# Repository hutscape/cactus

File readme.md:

# Cactus

> 🌵 Indoor WiFi-connected temperature and humidity sensor 🍶

Visit [hutscape.com/cactus](https://hutscape.com/cactus/) for more details.

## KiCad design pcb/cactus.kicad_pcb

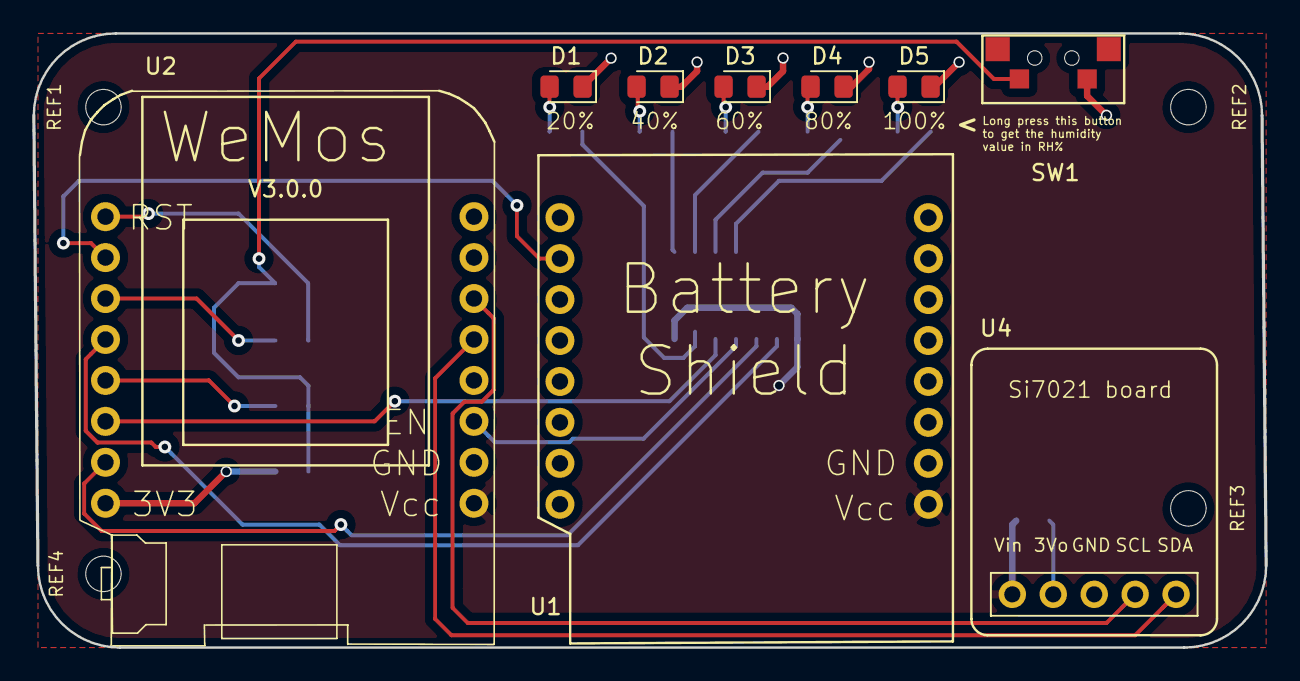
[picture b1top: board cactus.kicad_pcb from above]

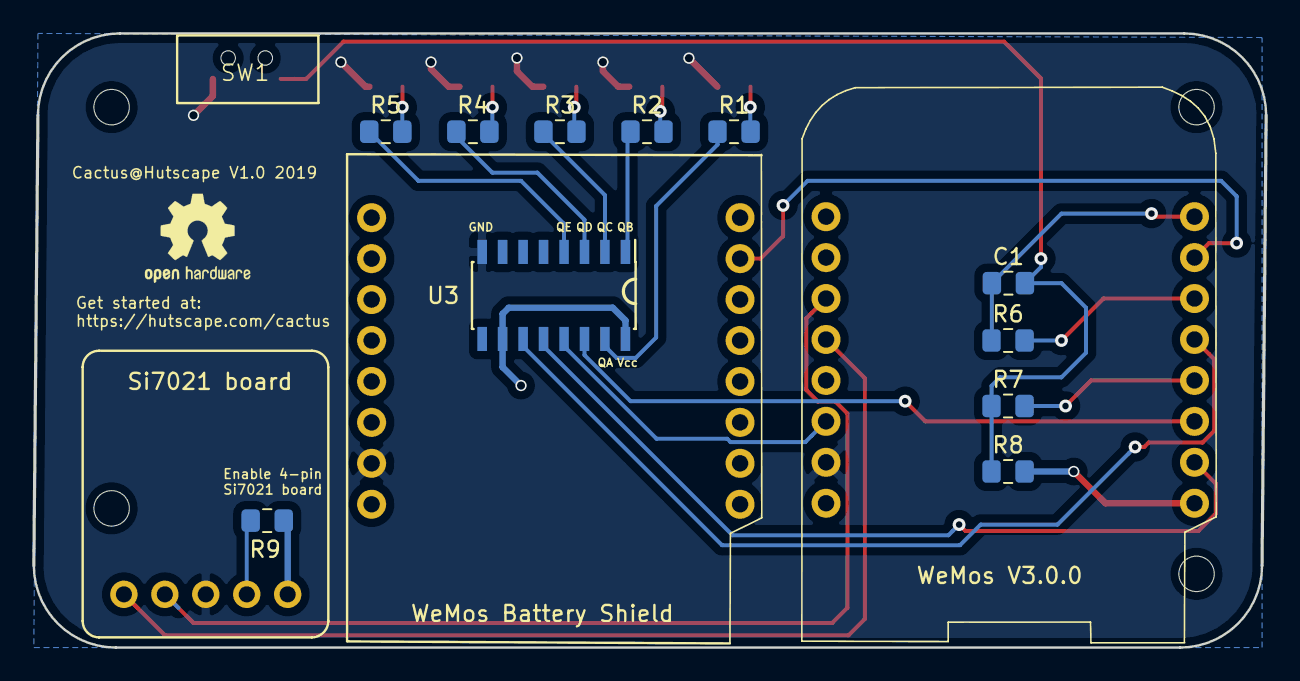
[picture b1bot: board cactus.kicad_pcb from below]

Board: 2 copper layers, 76.5 x 38.1 mm, 25 parts (12 on the bottom side), 25 nets.

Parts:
C1: 10u; C_0805_2012Metric_Pad1.15x1.40mm_HandSolder
D1, D2, D3, D4, D5: LED; LED_0805_2012Metric_Pad1.15x1.40mm_HandSolder
LOGO: OSHW-Logo2_7.3x6mm_SilkScreen
R1, R2, R3, R4, R5, R7: 1k; R_0805_2012Metric_Pad1.15x1.40mm_HandSolder
R6: 470; R_0805_2012Metric_Pad1.15x1.40mm_HandSolder
R8: 10k; R_0805_2012Metric_Pad1.15x1.40mm_HandSolder
R9: 0ohm; R_0805_2012Metric_Pad1.15x1.40mm_HandSolder
REF1, REF2, REF3, REF4: MountingHole_2.2mm_M2
SW1: SW_Push; Tactile_pushbutton
U1: WeMos_Battery_Shield; Battery_shield
U2: WeMos_D1_mini; D1_mini_board
U3: 74HC595; SOIC-16_3.9x9.9mm_P1.27mm
U4: Si7021_breakout; Si7021_breakout_board

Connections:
/3_3V: R8.2, U2.16
/A0: U1.10, U2.10
/D0: R6.2, U2.11
/D5: U2.12, U3.11
/D6: R7.2, U2.13
/D7: U2.14, U3.14
/D8: U2.15, U3.12
/EN: U2.3, U3.13
/I2C_SCL: U2.6, U4.2
/I2C_SDA: U2.5, U4.1
/QA: R1.1, U3.15
/QB: R2.1, U3.1
/QC: R3.1, U3.2
/QD: R4.1, U3.3
/QE: R5.1, U3.4
/RST: C1.1, R6.1, U2.9
GND: D1.1, D2.1, D3.1, D4.1, D5.1, SW1.2, U1.2, U2.2, U3.8, U4.3
unnamed: C1.2, R7.1, R8.1, SW1.1
unnamed: D1.2, R1.2
unnamed: D2.2, R2.2
unnamed: D3.2, R3.2
unnamed: D4.2, R4.2
unnamed: D5.2, R5.2
unnamed: R9.2, U4.4
VCC: R9.1, U1.1, U2.1, U3.10, U3.16, U4.5

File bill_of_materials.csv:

Designator,Value,Q,Package,Type,Category,Stock,Manufacturer Part No.,Manufacturer,"Vendor 
(Order link)",Unit Cost,Price type,Total cost,Ordered Cost,Ordered Quantity,Min Order Quantity,Description
C1,10u,1,SMD 0805,Capacitor 10uF 0805 SMD,Electronics,30,LMK212ABJ106KGHT,Taiyo Yuden,Mouser,$0.27,Exact,$0.27,$1.36,5,1,"SMD Multilayer Ceramic Capacitor, 10 µF, 25 V, 0805 [2012 Metric], ± 20%, X5R, GRM Series"
"D1, D2, D3, D4, D5",LED,5,SMD 0805,LED RED 0805 SMD,Electronics,32,150080RS75000,Wurth Electronics,Mouser,$0.26,Exact,$1.29,$2.58,10,1,"LED, Yellow, SMD, 0805, 20 mA, 2.1 V, 590 nm"
R6,470,1,SMD 0805,Resistor 470Ω 0805 SMD,Electronics,33,CRCW0805470RFKEAC,Vishay,Mouser,$0.15,Exact,$0.15,$0.76,5,1,"SMD Chip Resistor, 0805 [2012 Metric], 470 ohm, CR Series, 150 V, Thick Film, 125 mW"
"R1, R2, R3, R4, R5, R7",1k,6,SMD 0805,Resistor 1kΩ 0805 SMD,Electronics,18,,,Old Stock,$0.20,Estimated,,,,,"RES, THICK FILM, 1K, 1%, 0.125W, 0805"
R8,10k,1,SMD 0805,Resistor 10kΩ 0805 SMD,Electronics,31,CRCW080510K0FKEAC,Vishay,Mouser,$0.15,Exact,$0.15,$0.76,5,1,
R9,0ohm,1,SMD 0805,Resistor 0Ω 0805 SMD,Electronics,3,,,Old Stock,$0.15,Estimated,$0.15,,,,
R10,100k,1,TH,Resistor 100kΩ TH,Electronics,Yes,,,,,,,,,,100k resistor to patch WeMos battery shield
SW1,SW Push,1,SMD,Button,Electronics,14,,,Old Stock,$3.50,Estimated,$3.50,,,,
U1,WeMos Battery shield,1,TH,WeMos Battery shield,Electronics,,,,AliExpress,$0.79,Exact,$0.79,,,,WeMos Battery Shield
U2,WeMos D1 mini,1,TH,WeMos board,Electronics,Yes,,,Prototype stock,$2.50,Exact,$2.50,,,,WeMos D1 Mini V3.0.0
U3,74HC595,1,SOIC-16,Shift Register,Electronics,34,74HC595S16-13,DiodesZetex,RS Components,$0.20,Exact,$0.20,$5.05,25,25,16-pin shift register
U4,Si7021 breakout,1,TH,Sensor breakout board,Electronics,Yes,,,Prototype stock,$8.95,Exact,$8.95,,,,Si7021 Breakout Board
PCB,,1,,PCB,PCB,,,JLCPCB,JLCPCB,$2.00,Exact,$2.00,$2.00,5,5,
"REF1, REF2, REF3, REF4",2mm M2,4,M2,Nuts,Mechanical,Yes,,,Old Stock,$0.10,Estimated,$0.40,,,,
"REF1, REF2, REF3, REF4","2mm M2, 15mm height",4,M2,Spacers,Mechanical,Yes,,,Old Stock,$0.10,Estimated,$0.40,,,,
,Female pin header,5,,,Connector,,,,Old Stock,$0.05,Estimated,$0.25,,,,
,3.7 1200mAh LiPo,1,,,Battery,,,,12Geeks,$14.40,Exact,$14.40,$14.40,1,1,
,,,,,,,,,,,,,,,,
,,,,,,,,,,,,,,,,
,,,Total BOM items,36,,,BOM Cost breakdown,Percentage,Cost,,,,,,,
,,,Total BOM unique items,18,,,Electronics,50.73%,$17.96,,,,,,,
,,,Total unique electronics items,12,,,Battery,40.67%,$14.40,,,,,,,
,,,Total unique mechanical items,2,,,PCB,5.65%,$2.00,,,,,,,
,,,Total unique connector items,1,,,Mechanical,2.26%,$0.80,,,,,,,
,,,,,,,Connectors,0.71%,$0.25,,,,,,,
,,,Total cost,$35.41,,,,,,,,,,,,
,,,Total vendors,5,,,,,,,,,,,,

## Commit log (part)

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2019-04-02 [bom] Add KiCad generated BOM
2019-04-03 [mech] Add note on long press button on silkscreen
2019-04-03 [mech] Pass ERC with checks for courtyards
2019-04-03 [mech] Align reference and values for the LED array
2019-04-03 [mech] Change mounting hole diameter to 2mm
2019-04-05 [bom] Add order date for BOM
2019-04-05 [mech] Generate gerber
2019-04-05 [docs] Add manufacturing order date
2019-04-08 [docs] Add BOM receive order date
2019-04-12 [docs] Add timeline for manufacturing PCB
2019-04-13 [docs] Add checklist before buying a component
2019-04-15 [docs] Add checklist for buying components
2019-04-15 [docs] Add checklists and lessons learnt
2019-04-15 [docs] Add main component chip number for all modules
2019-04-15 [docs] Edit component parts
2019-04-20 [si] Add test code for LED and shift register
2019-04-20 [si] Test Si7021 temperature and humidity sensor
2019-04-20 [si] Add test firmware to test hardware integration on PCB
2019-04-22 Add temporary files to gitignore
2019-04-24 [si] Add final BOM and costing
2019-04-24 [si] Tweak the test firmware
2019-04-24 [si] Setup AP mode if WiFi credentials are not available
2019-04-24 [si] Initialise access point and webpage to input WiFi credentials
2019-04-25 [si] Send to cloud
2019-04-25 [si] Add code to test IFTTT POST data
2019-04-25 [si] Refactor HTTP POST code for host
2019-04-25 [si] Complete example for IFTTT POST Request
2019-04-25 [si] Post to IFTTT if the WiFi credentials are available
2019-04-26 [si] Add instructions to POST to IFTTT
2019-04-26 [si] Add notes on what happens if the WiFi cannot be connected
2019-04-28 Create and connect to IFTTT via TLS
2019-04-28 [si] Add component code for measuring LiPo voltage and debugging mDNS
2019-04-29 [docs] Rename d-flip-flop firmware file
2019-04-29 [docs] Rename display-humidity-with-led firmware file
2019-04-29 [docs] Rename ifttt-post-data firmware file
2019-04-29 [docs] Rename long-sleep-or-button-press firmware file
2019-04-29 [docs] Add sections for various component testing
2019-04-29 [docs] Rename measure battery voltage firmware file
2019-04-29 [docs] Rename sensor-si7021 firmware file
2019-04-29 [docs] Rename wakeup-periodically firmware file
2019-04-29 [si] Add units for battery voltage measurement
2019-04-30 [si] Add battery version and 100k ohm instructions
2019-04-30 [docs] Amend all main.ino to parent folder names for Arduino IDE
2019-04-30 [docs] Add step to make install
2019-04-30 [si] Test battery voltage data with LiPo
2019-04-30 [si] Move test firmware into a seperate folder for Arduino IDE
2019-04-30 [si] Read battery voltage and send to IFTTT with TLS
2019-04-30 [si] Sleep and wakeup every 1 hour
2019-04-30 [si] Update AP webpage screenshot
2019-04-30 [si] Reduce number of steps for getting started
2019-05-01 [si] Refactor functions into logically similar blocks
2019-05-01 [si] Fix mDNS issue by updating ESP8266 Arduino firmware to latest branch
2019-05-01 [docs] Add link to firmware commit hash because of mDNS patch
2019-05-02 [si] Do not display LEDs if it wakes up automatically after timer interrupt
2019-05-02 [docs] Add a note on mechanical housing and an opening for env sensors
2019-05-02 [si] Amend variable names and change sleep interval to 1 hour
2019-05-02 [si] Reduce interval for debugging
2019-05-04 [si] Always wakeup without radio to save power
2019-05-05 [docs] Add arduino-cli temporary files to gitignore
2019-05-05 [si] Increase sleep count and do task when the interval is over
2019-05-05 [si] Wakeup without WiFi radio to save power, but connect when the sleep count is over
2019-05-05 [si] Test git co-authored by
2019-05-05 [si] Setup Access Point when WiFi connection fails
2019-05-05 [si] Connect to WiFi when credentials are stored
2019-05-05 [si] Add mDNS to access cactus.local to configure WiFi
2019-05-06 [si] Add a ticker example
2019-05-06 [si] Send a command through the serial monitor
2019-05-06 [si] Blink in AP mode
2019-05-06 [si] Fix blinking in AP mode
2019-05-06 [si] Test out filling a form page and redirect upon sucess in AP mode
2019-05-06 [si] Measure sensor and connect to WiFi on button press or wakeup
2019-05-06 [si] Amend bar display for humidity
2019-05-06 [si] Set interval ping back to cloud at 4 hours
2019-05-07 [docs] Add CNAME
2019-05-07 [docs] Remove CNAME
2019-05-07 [docs] Move component code to erase WiFi credentials to another repo
2019-05-07 [docs] Move component code IFTTT GET request to another repo
2019-05-07 [docs] Move component code long sleep or on button press to another repo
2019-05-07 [docs] Move checklists to another repo
2019-05-07 [docs] Move components to another repo
2019-05-09 [deploy] Complete schedule timeline
2019-05-14 [docs] Add lesson learnt on making at least 2 units
2019-05-17 [deploy] Ping back to cloud after 6 hours to save battery
2019-05-23 [deploy] Add actual vs calculated power consumption
2019-05-23 [docs] Transfer library files as git submodule
2019-05-24 [docs] Update kicad library
2019-05-26 [deploy] ignore cpplint rules
2019-05-26 [deploy] Fix cpplint errors
2019-06-01 [bug] Remove extra via in R2. Fixed #10
2019-06-04 [footprint] Add more pin notes on silkscreen
2019-06-04 [test] Improve test firmware
2019-06-06 [firmware] Add tweaks for firmware to enhance battery life
2019-06-06 [docs] Add maintenance notes on charging and flashing firmware
2019-06-30 [docs] Add warning signs for battery shield and USB connectors
2019-07-12 [docs] Fix path
2019-07-12 [docs] Fix path to the correct project
2019-07-12 [docs] Display tabs with pages and sequences
2019-07-14 [docs] Complete design of the getting started page
2019-07-14 [docs] Add prototype photos on the front page
2019-07-14 [docs] Design page for software
2019-07-15 [docs] Styles references page
2019-07-15 [docs] Add link to KiCad files
2019-07-15 [docs] Style design page with power tree and state machine
2019-07-15 [docs] Style mechanical page
2019-07-15 [docs] Render BOM page
2019-07-15 [docs] Add test firmware to software page
2019-07-15 [docs] Refer to config yml for github url
2019-07-16 [docs] Move software related images into one directory
2019-07-16 [docs] Fix hardware link
2019-07-16 [docs] Add back state machine
2019-07-17 [docs] Add GA
2019-07-17 [docs] Improve vendor listing
2019-07-18 [docs] New square prototype photos
2019-07-18 [docs] Update git submodule
2019-07-18 [docs] Simplify readme
2019-07-19 [docs] Update styles for gantt chart
2019-07-19 [docs] Remove BOM columns
2019-07-22 [docs] Add license
2019-07-22 [docs] Add design to a common layout
2019-07-22 [docs] Add starter images from submodule
2019-07-22 [docs] Add references template
2019-07-22 [docs] Add schedule layout
2019-07-22 [docs] Remove lessons data and add it into the page
2019-07-22 [docs] Use protocol relative url
2019-07-23 [docs] Add completion date in header
2019-07-23 [docs] Add note on editing
2019-07-24 [docs] Add a subtitle for v2 lessons learnt
2019-07-25 [docs] Update submodule
2019-07-25 [docs] Amend mechanical headings
2019-07-29 [docs] Add more power info
2019-08-01 [docs] Fix iBOM URL
2019-08-01 [docs] Add space in BOM vendors
2019-08-01 [docs] Hide iBOM on touch devices
2019-08-02 [docs] Sync design page
2019-08-04 [docs] Remove non-data list items from BOM CSV
2019-08-07 [docs] Add currency conversion for unit cost and total BOM cost
2019-08-10 [firmware] Add index.html code for web config of WiFi and IFTTT
2019-08-10 [firmware] Add web page in AP mode as a header file
2019-08-10 [firmware] Add web html to config page
2019-08-12 [schematic] Add a note on a bodge to control sensor Vin digitally
2019-08-12 [docs] Add hyperlinks to getting started images
2019-08-17 [docs] Fix YouTube
2019-08-17 [docs] Add fixed navbar
2019-08-26 [docs] Standardise project properties
2019-09-05 [docs] Add scripts folder as a git submodule
2019-09-05 [docs] Fix path for git submodule
2019-09-16 [docs] Update submodules and gems
2019-09-16 [docs] Add icons
2019-09-18 [docs] Move power diagrams to different folder
2019-09-18 [docs] Take mechanical details from data
2019-10-05 [docs] Transfer references to project specific repo
2019-10-09 ci: add ci for jekyll
2019-10-11 fix: change unit cost from string to float for proper sorting
2019-10-12 fix: display just vendor name if vendor link is not available
2019-10-24 feat: change footprint to layout naming
2019-10-28 feat: add button link for gerber files
2019-11-07 chore: update submodules
2019-11-28 chore: update KiCad 5.1.5
2019-12-03 refactor: change navbar components to tutorials
2020-05-10 docs: add v2 feature to make measurement interval configurable
2021-03-30 Bump kramdown from 2.3.0 to 2.3.1
    Bumps [kramdown](https://github.com/gettalong/kramdown) from 2.3.0 to 2.3.1.
    - [Release notes](https://github.com/gettalong/kramdown/releases)
    - [Changelog](https://github.com/gettalong/kramdown/blob/master/doc/news.page)
    - [Commits](https://github.com/gettalong/kramdown/commits)
2021-03-30 chore: improve make with bundle exec
2021-05-06 chore: update dependancies
2021-06-26 chore: updgrade dependancies
2021-06-27 chore: remove unused gem
2021-06-30 docs: change description and update readme
2021-07-15 chore: update addressable dependancy
2021-08-10 chore: update year in license
2021-08-23 refactor: combine lessons, references and schedule pages into others
2021-08-23 refactor: combine design, power and mechanical into design
2021-08-26 refator: seperate layouts and includes as submodules
2021-09-10 fix: reset fonts after inserting iBom
2021-10-07 fix: add example page content in layouts
2021-10-20 docs: reword prequisites to simpler and similar
2021-10-23 chore: update files
2021-12-17 refactor: change styling for dependancies, pre-requisites, and components
2022-03-09 feat: add favicons to project head
2022-03-09 chore: update anchor.js
2022-03-18 chore: update KiCad6 and ruby gems on Monterey
2022-04-13 docs: remove url in similar project section
2022-04-13 refactor: remove _data/project.json and combine into _config.yml
2022-04-13 refactor: remove unused version
2022-04-20 "refactor: sync status tags and update footer"
2022-04-20 "refactor: put the download links first on the start page"
2022-04-20 "refactor: seperate code into more partials"
2022-04-21 "feat: add new git submodule and install themupon creating new project"
2022-04-21 "refactor: seperate Design page into more partials"
2022-05-13 "feat: add VSCode text editor and FreeCAD files to gitignore"
2022-05-18 "feat: add 18650 battery 3D model to KiCad library"
2022-05-19 "feat: add /case layout for projects with enclosure designs"
2022-05-19 "refactor: improve FreeCAD file name and link"
2022-07-21 refactor: rename directory from hardware to pcb
2022-07-21 "fix: change link to code images"
2022-07-22 refactor: move software section to code
2022-07-25 feat: add 3d printed case photos
2022-07-25 refactor: move code list to includes
2024-02-26 feat: update submodules for unique SMT, DNP and TH BOM parts
2024-02-29 chore: update submodule to fix image url display for relative project paths
2024-02-29 chore: update submodules to display manufacturing params for case
2024-03-13 chore: update submodules to display cost breakdown section
2024-03-15 chore: update submodules to display software bill of materials
2024-03-27 refactor: divide others page into csq and resources
2024-03-29 chore: update submodule to add a link to FreeCAD file download
2024-04-01 chore: update submodules to hyperlink images
2024-04-11 feat: add a new power page
2024-04-11 docs (power): remove HTML and convert content to only markdown
2024-04-12 refactor: simplify putting content on start page with only Markdown
2024-05-04 chore: update submodules to add a link to download demo code
2024-05-04 docs: remove link to demo firmware
2024-05-06 refactor (docs): simplify iteration ideas into one big list
2024-10-11 chore: update submodule to fix checkbox mobile view
2024-11-08 docs: update navbar
2024-11-14 chore: update submodule to conditionally display edit button
